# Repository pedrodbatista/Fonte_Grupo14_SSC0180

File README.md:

# Projeto de Eletrônica - Fonte Váriavel de 3-12V / 100mA
* **Disciplina:** *SCC0180* - Eletônica para Computação (2021)
* **Professor:** Eduardo do Valle Simões (simoes@icmp.usp.br)

### Grupo
Projeto realizado pelo Grupo 14:
* Fábio Verardino de Oliveira - N. USP: 12674547
* Fabio Henrique Alves Cavaleti - N. USP: 11200550
* Gabriel Fachini - N. USP: 11953481
* Pedro Dias Batista - N. USP: 10769809

---

## Especificações
Para o projeto, deve ser construída uma fonte de retificadora de tensão contínua e variável, entre 3V e 12V. Além disso a fonte deve ser capaz de fornecer 100mA. A entrada da fonte é uma onde senoidal de corrente alternada, com tensão de 127V e frequência de 60Hz.

## Desenvolvimento do circuito
A teoria por traz dos estágios da fonte variável, além dos cálculos que leveram à escolha dos valores dos componentes estão expostas no seguinte documento: [PDF Trabalho de Eletrônica](assets/Trabalho_Eletronica.pdf).

## Circuito no Simulador Falstad
O circuito foi construído no simulador online [Falstad](http://falstad.com/circuit/circuitjs.html), a fim de confirmar o funcionamento da fonte e ajustar os valores dos componentes.

O circuito do projeto pode ser acessado no seguinte link: [Fonte Variável - Falstad][9].

[9]: http://falstad.com/circuit/circuitjs.html?ctz=CQAgjCAMB0l3BWEBOaB2AHAZmcjAWBLANgwCYwsQEzqR8qEBTAWjDACgA3EFsyDODTFe-QWQyDI4EMWlgyaKCDKxkDZAjCQyOLGE1UYCDgHdRAoSL6Ww+fFDMXBdhywzz7j8zfGTnIFiQDpBO7tJBbmKBwY4AJspkZA4e4HIqIHFMAGYAhgCuADYALhwJqWDprir40rRZeUWlCXXJsg6RGQ0FJWXtMQ7VyXWZOT2lPsSDXlPgXqHms9UV804V6SshYbOdO7ELiW1sIklbPpUqRxckUk5DtSqWw96816SPgjcvEp-v+DvvA5YAg1aT-BzPUJYBwALyYADsmAAnNhGcDoMCsJQjSjgDgw+gAwTg0EZOGIlGUJwk540cQPUJgNAOOmk1mdCAIeBQWCQJAAJSYAGcAJZC4q5eEAYyYHCR1AkAwVvykjzg1KJysCgKcWH4pL18kVQP1CkEUyNt0WDzNsjQtFtB2I9vAiudtDICBEoWK1C8ilo7pULvkomgxAQ+DA5HsyBI6ij2IxXLQWH0pDIUyIHTgo0avUWLp+IFTJ38B3Z71L2tu8urxerXyNoQAKrxNrw9iF6Dy7DyBEzXLgMF6FDoqFhoFH8MIEFziMRM8JMSwk7hkBwpR9SdEvrQYPAlGAENAEJp-nZksRKlf+5BOOZi89DaTOPKX8+QZD6OrH08Hk+DJOLu7zFk2HAAPbKLMYKQLgaTSDA3b7oEkEoP0sHwfqk4OhkyCoVBaYYT+WERNAHoZERWBofqMEkfh+oHgoSBUB6ERofoxG1KRPK0BCgQQNRQA

## Esquemático e PCB do circuito no Autodesk EAGLE
Após a simulação do circuito. Foi construído um esquemático do circuito no software Autodesk EAGLE, com o intuito de criar, depois, um modelo da placa de circuito da fonte.

A partir desse esquemático, o mesmo software foi utilizado para montar o modelo da PCB do circuito da fonte.

* O transformador foi deixado de fora do esquemático pois ocupa muito espaço. O jumper JP1 representa os pontos de conexão da bobina secundária.
* Os arquivos do projeto no EAGLE estão no repositório do projeto.

## Componentes utilizados

A lista a seguir contém os componentes utilizados na montagem da fonte, além de links para comprá-los e seus preços:

| Componente         | Especificações      |Quantidade | Preço Unitário | Total    |
|---                 |---                  |--:        |---:            |---:      |
| [Transformador][1] | 127V -> 18V         | 1         | R$ 27.99       | R$ 29.99 |
| [Capacitor][2]     | 1mF / 25V           | 1         | R$ 0.46        | R$ 0.46  |
| [Diodo][3]         | 1N4007              | 4         | R$ 0.10        | R$ 0.40  |
| [Resistor][4]      | 330Ω                | 1         | R$ 0.18        | R$ 0.18  |
| [Resistor][5]      | 2kΩ                 | 1         | R$ 0.05        | R$ 0.05  |
| [Diodo Zener][6]   | V<sub>Z</sub> = 13V | 1         | R$ 0.19        | R$ 0.19  |
| [Potênciometro][7] | 5kΩ                 | 1         | R$ 1.99        | R$ 1.99  |
| [Transistor][8]    | 2N2222              | 1         | R$ 0.26        | R$ 0.26  |
|                    |                     |           |**Total**      | R$ 33.52 |

[1]: https://www.soldafria.com.br/transformador-18v-500ma-entrada-110-220vac
[2]: https://www.baudaeletronica.com.br/capacitor-eletrolitico-1000uf-25v.html
[3]: https://www.baudaeletronica.com.br/diodo-1n4007.html
[4]: https://www.baudaeletronica.com.br/resistor-330r-5-1w.html
[5]: https://www.baudaeletronica.com.br/resistor-2k-5-1-4w.html
[6]: https://www.baudaeletronica.com.br/diodo-zener-1n4743-13v-1w.html
[7]: https://www.baudaeletronica.com.br/potenciometro-linear-de-5k-5000.html
[8]: https://www.baudaeletronica.com.br/transistor-npn-2n2222.html

* Alguns dos valores dos componenetes foram alterados para atender à disponibilidade do mercado. O funcionamento da fonte não é prejudicado ao utilizar-se desses componentes.

## Vídeo explicativo

Também foi gravado, pelos integrantes do grupo, um vídeo explicando o funcionamento do circuito e dos componentes que o compõem, além dos calculos realizados para a escolha daqueles.

* [Vídeo do projeto](https://youtu.be/JVlfiyRQYMs)

---

## Agradecimento

Os integrantes do grupo gostariam de agradecer ao professor Eduardo Simões e ao monitor Gabriel Kuabara por toda a ajuda durante a realização do projeto.

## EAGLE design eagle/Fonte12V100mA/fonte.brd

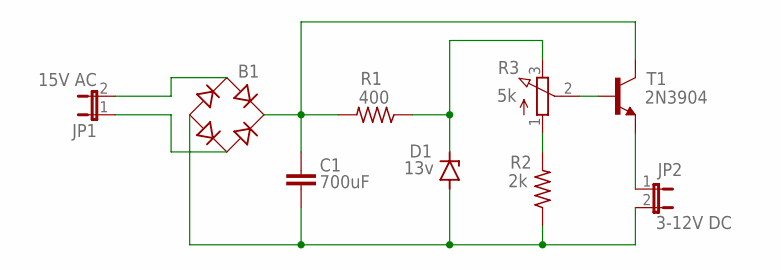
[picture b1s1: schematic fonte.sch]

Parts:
B1: B-DIL
C1: 700uF; C025-025X050
D1: 13v; SOD81
JP1: 15V AC; JP1
JP2: 3-12V DC; JP1
R1: 400; 0204/7
R2: 2k; 0204/7
R3: 5k; 3RP/1610N
T1: 2N3904; TO92

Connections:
unnamed: B1.AC1, JP1.2
unnamed: B1.AC2, JP1.1
unnamed: R3.2 (S), T1.2 (B)
unnamed: B1.-, C1.2, D1.A, JP2.2, R2.1
unnamed: R2.2, R3.1 (A)
unnamed: D1.C, R1.1, R3.3 (E)
unnamed: JP2.1, T1.3 (E)
unnamed: B1.+, C1.1, R1.2, T1.1 (C)

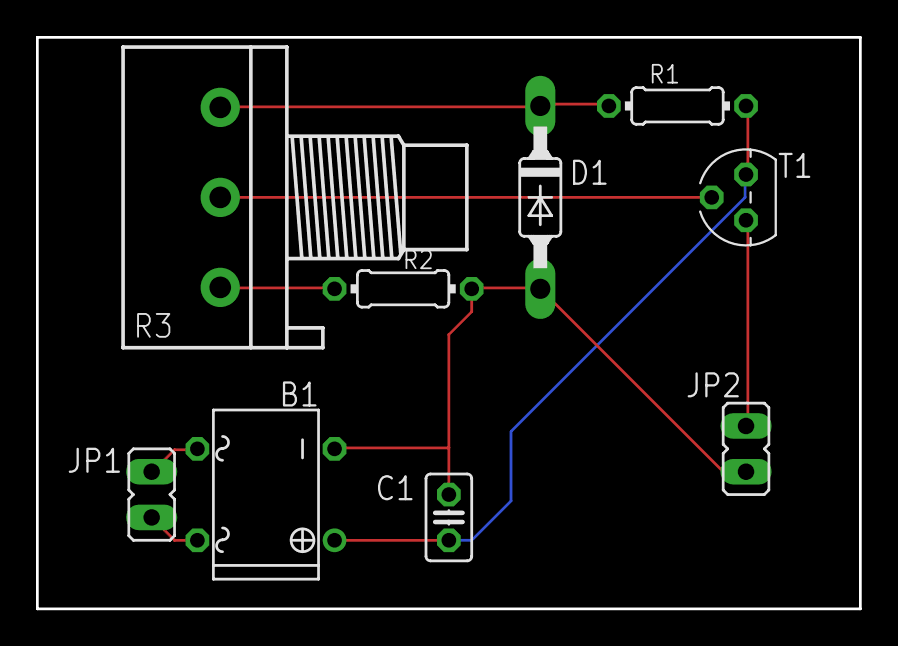
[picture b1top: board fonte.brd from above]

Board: 2 copper layers, 45.7 x 31.8 mm, 9 parts (0 on the bottom side), 8 nets.

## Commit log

2021-07-27 Arquivos do projeto, imagens e README adicionados
2021-07-27 Atualizaçao do README
2021-07-27 Adicionado link do video ao README
2021-07-27 Observação sobre o transformador
